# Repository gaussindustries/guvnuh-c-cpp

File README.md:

# Guv’nuh – Embedded Governor Development Platform (C/C++ Edition)

A laboratory-scale governor that transforms a 0.5 HP induction machine into a **programmable micro-generator**, serving as a complete test-bed for turbine-control firmware, load-response algorithms, and networked telemetry.

---

## Project Purpose

> Deliver a robust, real-time **governor controller** demonstrating the embedded firmware, control theory, and safety-engineering competencies required for professional embedded and power-electronics development.

This version focuses on **C/C++**, deterministic control, and FreeRTOS-based task management across dual MCUs (STM32 + ESP32).
A remote visualization stack hosted on a **VPS** provides live telemetry, replay, and demo access.

---

## Functional Scope (Phase-1)

| ID   | Requirement                              | Target Value / Notes              |
| ---- | ---------------------------------------- | --------------------------------- |
| F-01 | Real-time phase synchronization          | ±1 Hz tolerance @ 50 Hz nominal   |
| F-02 | Load response under transient excitation | < 100 ms stabilization            |
| F-03 | Encoder-PLL speed estimation             | ±0.5 % accuracy, 0–1800 RPM range |
| F-04 | Modbus-RTU link to VFD                   | 115 200 baud, master-mode         |
| F-05 | Isolated MCU bridge (COBS + CRC16)       | 1–3 Mbps, full-duplex DMA         |
| F-06 | MQTT/HTTPS uplink                        | TLS 1.3, 10–50 Hz telemetry       |

Phase-2 will migrate from Modbus RTU to **EtherCAT**, enabling deterministic distributed control and multi-node synchronization.

---

## Repository Structure

```
├── stm32/                  ↳ Real-time control firmware (C/C++ + FreeRTOS)
│   ├── app/                ↳ Config · telemetry packer · command handler
│   ├── control/            ↳ PLL · SEIG excitation · protections
│   ├── drivers/            ↳ ADS131M04 · encoder · RS-485 (Modbus master)
│   │   ├── ads131/
│   │   ├── encoder/
│   │   └── rs485_modbus/
│   ├── middleware/
│   │   ├── link/           ↳ UART DMA · COBS · CRC16
│   │   └── utils/          ↳ ring buffers · fixed-point helpers · logging shims
│   ├── rtos/
│   │   ├── tasks/          ↳ task_control · task_link · task_telemetry
│   │   ├── freertos_config/↳ FreeRTOSConfig.h (STM32-specific)
│   │   └── hooks/          ↳ idle/tick/malloc-failed hooks · trace points
│   ├── bsp/                ↳ clocks · pins · board init
│   ├── CMakeLists.txt
│   └── main.c
│
├── esp32/                  ↳ Networking & UI gateway (C/C++ + ESP-IDF/FreeRTOS)
│   ├── link/               ↳ UART bridge (COBS/CRC, backpressure)
│   ├── net/                ↳ MQTT/HTTPS client · reconnect/backoff · SNTP
│   ├── ota/                ↳ OTA + optional STM32 relay
│   ├── ui/                 ↳ Minimal local status HTTP server
│   ├── rtos/
│   │   └── tasks/          ↳ task_mqtt · task_uart_bridge · task_time_sync
│   ├── CMakeLists.txt
│   └── main.cpp
│
├── common/                 ↳ Shared C/C++ headers and libs (built for both MCUs)
│   ├── include/            ↳ cobs.h · crc16.h · proto.hpp · telem.hpp
│   └── src/                ↳ cobs.c · crc16.c
│
├── third_party/            ↳ External deps (optional)
│   └── freertos-kernel/    ↳ Vendored FreeRTOS for STM32 (if used)
│
├── docs/                   ↳ Architecture · control flow · standards & refs
│   └── 10_architecture/    ↳ architecture.md · diagrams
│
├── tests/                  ↳ HIL · soak · property/regression tests
├── tools/                  ↳ Telemetry schema · payload fuzzers
├── build/                  ↳ Out-of-tree build artifacts
├── ci/                     ↳ CI/CD scripts (firmware builds, static analysis)
└── README.md
```

A separate repository, **`guvnuh-digest`**, will handle ingestion, visualization, and long-term storage of telemetry data.

---

## Technology Stack

| Layer           | Implementation / Hardware                      | Rationale                                                             |
| --------------- | ---------------------------------------------- | --------------------------------------------------------------------- |
| **Control MCU** | STM32H753 (NUCLEO-H753ZI) + C/C++ + FreeRTOS   | Deterministic real-time control                                       |
| **Gateway MCU** | ESP32 (Wi-Fi/Ethernet) + ESP-IDF               | Secure MQTT/HTTPS uplink                                              |
| **Fieldbus**    | Modbus-RTU → EtherCAT (Phase-2)                | Legacy + modern compatibility                                         |
| **Sensing**     | ADS131M04 (ΣΔ ADC) + Encoder (AMT10) + INA240s | High-accuracy power measurement                                       |
| **Comms Link**  | UART DMA · COBS · CRC16 (0xA001)               | Binary framing · no delimiters                                        |
| **Data Layer**  | MQTT + TLS + CBOR telemetry                    | Compact · loss-tolerant                                               |
| **Backend**     | Dioxus Fullstack + SurrealDB                   | Unified Rust-based web stack handling API, storage, and visualization |
| **RTOS Choice** | FreeRTOS (primary) · Zephyr (candidate)        | Demonstrates embedded RTOS skills                                     |

---

## Phase-1 Milestones

| Deliverable                  | Competence Demonstrated         |
| ---------------------------- | ------------------------------- |
| UART-DMA loopback both MCUs  | Low-level peripheral bring-up   |
| COBS + CRC link validated    | Deterministic packet transport  |
| SPI DMA ADS131 stream        | High-rate ADC pipeline          |
| Encoder + PLL speed tracking | Signal processing + control     |
| Modbus master → VFD control  | Industrial protocol integration |
| Load response demo           | Real-time loop tuning           |
| MQTT telemetry uplink        | Network gateway implementation  |

---

## Build & Flash

```bash
# STM32 (FreeRTOS build)
cmake -B build/stm32 -S stm32 -DCMAKE_BUILD_TYPE=Release
cmake --build build/stm32 -j
openocd -f interface/stlink.cfg -f target/stm32h7x.cfg \
  -c "program build/stm32/firmware.elf verify reset exit"

# ESP32 (ESP-IDF)
idf.py set-target esp32
idf.py build flash monitor
```

---

## Visualization & Web Interface

All telemetry is published to a **VPS** via MQTT for digestion and display by a separate repository:

* **`guvnuh-digest`** → Ingests, normalizes, and stores data
* **`guvnuh-web`** → Presents dashboards, demo playback, and system status

This separation ensures the embedded side remains deterministic while still providing rich insights into control performance and system behavior.

---

## Standards & Practices

* **IEC 61508 SIL-2** – Safety life-cycle principles
* **IEC 60204-1** – Control-power segregation
* **ISA-50 / Modbus-RTU** – Industrial protocol reference
* **IEEE 519** – Power quality and harmonic analysis
* **MISRA-C 2012** – Static analysis and safe C subset

---

© 2025 Gauss Industries · MIT License

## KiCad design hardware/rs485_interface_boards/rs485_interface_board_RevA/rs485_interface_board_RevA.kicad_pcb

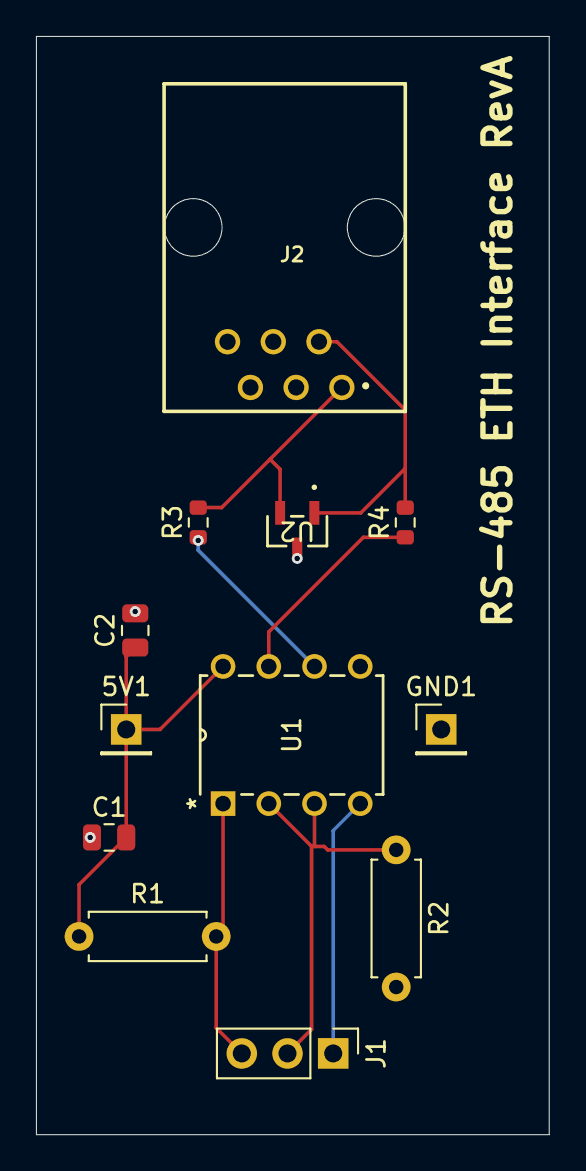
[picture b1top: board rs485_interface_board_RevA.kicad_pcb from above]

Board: 2 copper layers, 28.5 x 61.0 mm, 12 parts (0 on the bottom side), 9 nets.

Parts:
5V1: Conn_01x01; PinHeader_1x01_P2.54mm_Vertical
C1, C2: 100 nf; C_0805_2012Metric
GND1: Conn_01x01; PinHeader_1x01_P2.54mm_Vertical
J1: Conn_01x03; PinHeader_1x03_P2.54mm_Vertical
J2: 615006141121
R1, R2: 10k; R_Axial_DIN0207_L6.3mm_D2.5mm_P7.62mm_Horizontal
R3, R4: 10 Ohm; R_0603_1608Metric
U1: SN65HVD3082EP; sn65hvd3082
U2: SM712.TCT; SOT23_SEM

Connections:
+5V: 5V1.1, C1.2, C2.1, R1.1, U1.8 (VCC)
GND: C1.1, C2.2, GND1.1, J2.3, R2.2, U1.5 (GND), U2.3
unnamed: J1.1, U1.4 (D)
unnamed: J1.2, R2.1, U1.2 (*RE), U1.3 (DE)
unnamed: J1.3, R1.2, U1.1 (R)
unnamed: J2.1, R3.2, U2.2
unnamed: J2.2, R4.2, U2.1
unnamed: R3.1, U1.6 (A)
unnamed: R4.1, U1.7 (B)

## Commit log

2025-10-30 init commit, folder struct,README.md
2025-10-30 updated architecture.md
2025-10-30 updated file struct for freertos
2025-10-30 updated readme to reflect new folder struct
2025-11-05 Add STM32CubeH7 as submodule
2025-11-07 created rs45 - modbus interface RevA board
2025-11-07 completed rs-485 eth rev a board, generated pcb
